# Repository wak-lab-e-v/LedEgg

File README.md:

# LedEgg

WAK-Lab project 
* Atiny 25/45/85 based
* 3 74HC595D 8-bit serial-in, serial or parallel-out shift register with output latches
* 21 LEDs

## Led chain
3 positions are not connectet to a led but take a place in the serial stream of 3 bytes

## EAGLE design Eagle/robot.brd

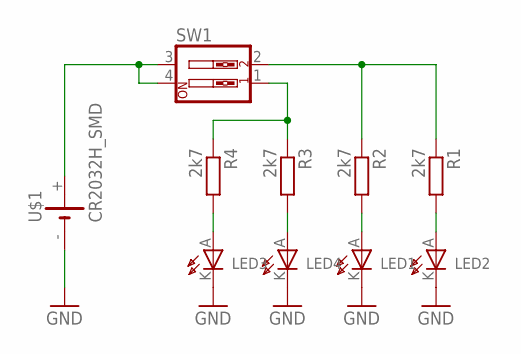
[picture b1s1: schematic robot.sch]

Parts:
LED1, LED2: LEDREAR; 3MM_REAR
LED3, LED4: LED3MMH; 3MM_H
R1, R2, R3, R4: 2k7; 0204/7
SW1: SW_DIP-2; EDG-02
U$1: CR2032H_SMD

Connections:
GND: LED1.K, LED2.K, LED3.K, LED4.K, U$1.-
unnamed: LED4.A, R3.2
unnamed: LED3.A, R4.2
unnamed: R1.1, R2.1, SW1.2
unnamed: R3.1, R4.1, SW1.1
unnamed: SW1.3, SW1.4, U$1.+
unnamed: LED1.A, R2.2
unnamed: LED2.A, R1.2

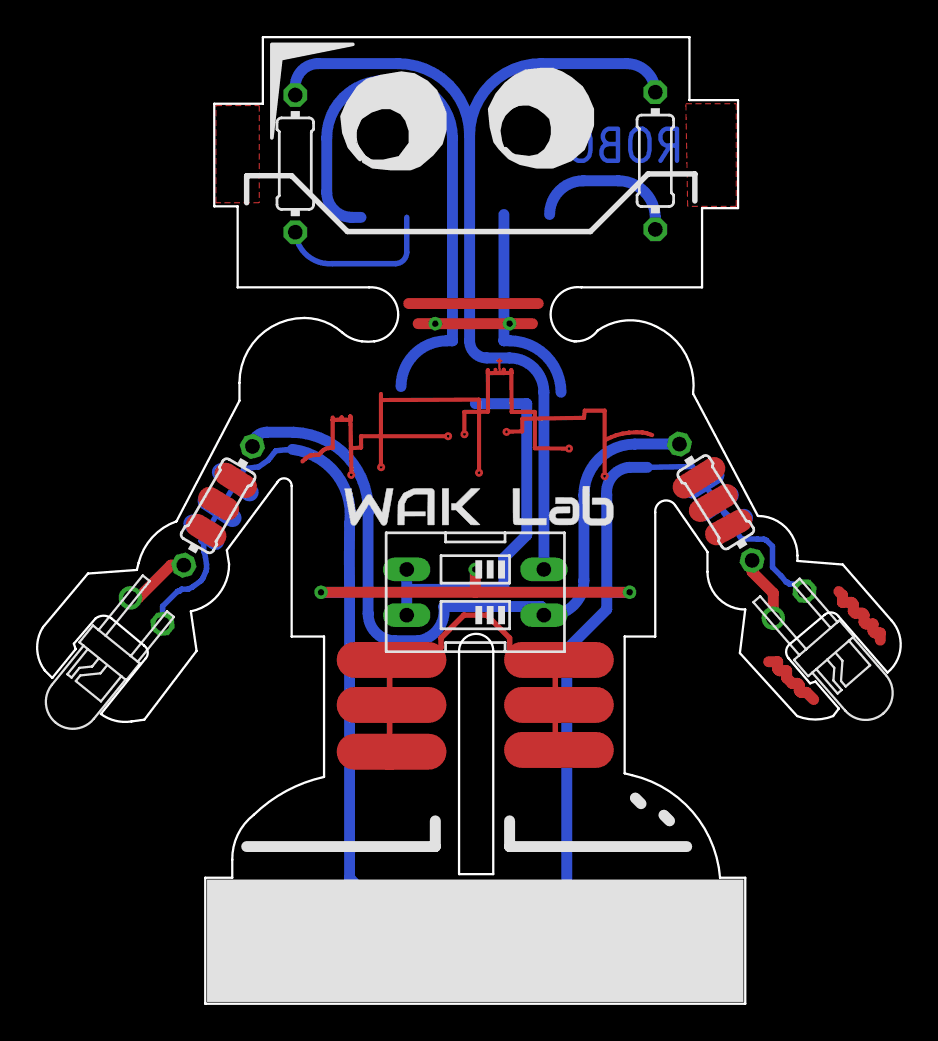
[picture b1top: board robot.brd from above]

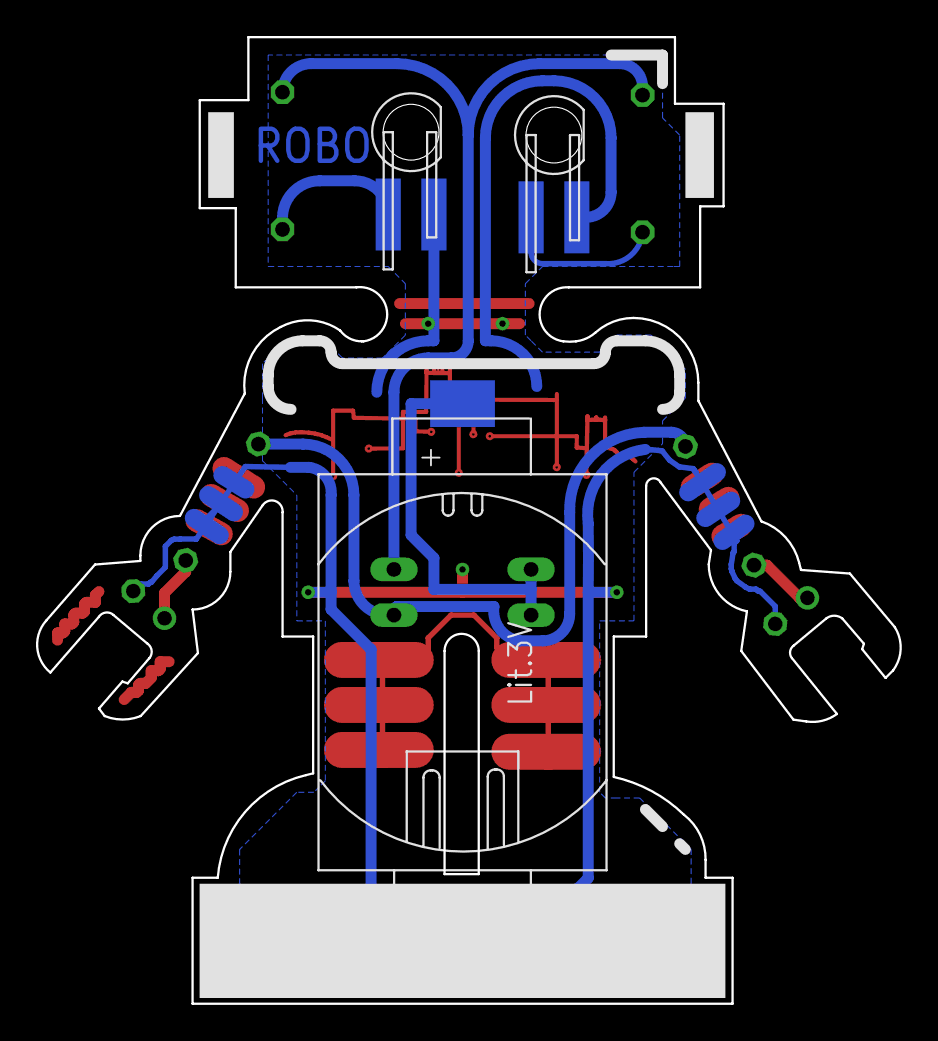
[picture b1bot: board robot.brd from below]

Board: 2 copper layers, 48.0 x 53.7 mm, 10 parts (3 on the bottom side), 8 nets.

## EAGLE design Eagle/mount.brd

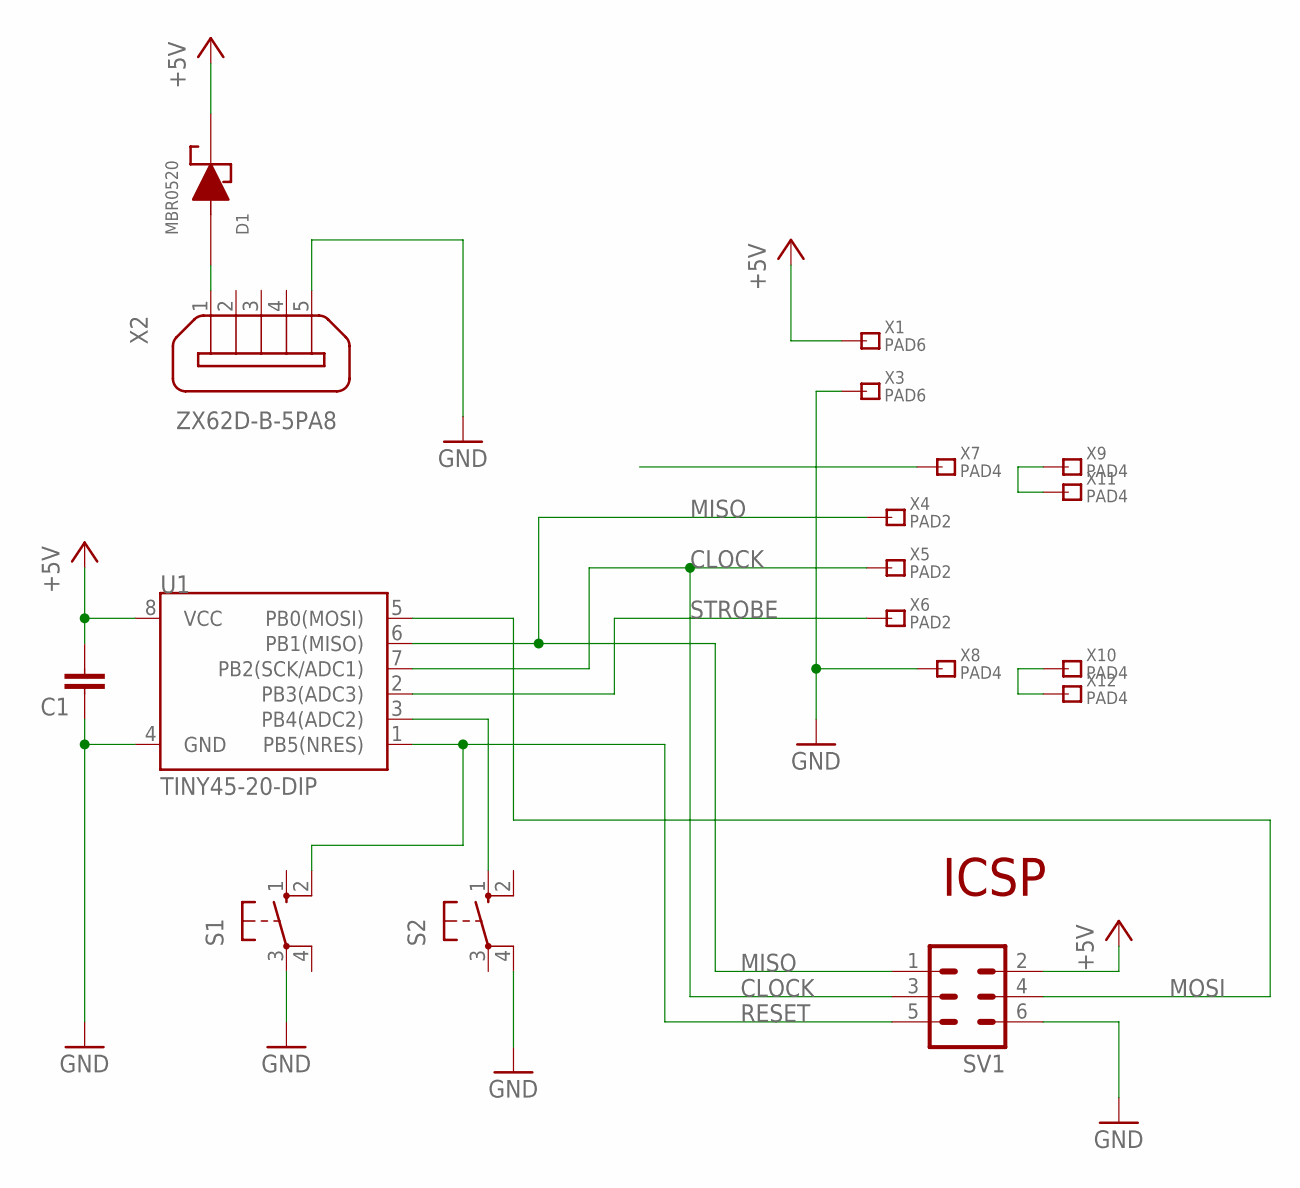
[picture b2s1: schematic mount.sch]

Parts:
C1: C-EUC0805; C0805
D1: MBR0520; SOD-123
S1, S2: 10-XX; B3F-10XX
SV1: MA03-2
U1: TINY45-20-DIP; DIP08_MCU
X1, X3: PAD6; SMDPAD
X2: ZX62D-B-5PA8
X4, X5, X6: PAD2; SMDPAD_S
X7, X8, X9, X10, X11, X12: PAD4; SMDPAD_M

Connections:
+5V: C1.2, D1.1 (CA), SV1.2, U1.8 (VCC), X1.P$1
CLOCK: SV1.3, U1.7 (PB2(SCK/ADC1)), X5.P$1
GND: C1.1, S1.3, S2.4 (P1), SV1.6, U1.4 (GND), X2.5, X3.P$1, X8.P$1
MISO: SV1.1, U1.6 (PB1(MISO)), X4.P$1
MOSI: SV1.4, U1.5 (PB0(MOSI))
unnamed: X9.P$1, X11.P$1
unnamed: X10.P$1, X12.P$1
unnamed: S2.1 (S), U1.3 (PB4(ADC2))
unnamed: D1.2 (AN), X2.1
RESET: S1.2 (S1), SV1.5, U1.1 (PB5(NRES))
STROBE: U1.2 (PB3(ADC3)), X6.P$1

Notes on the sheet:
ICSP

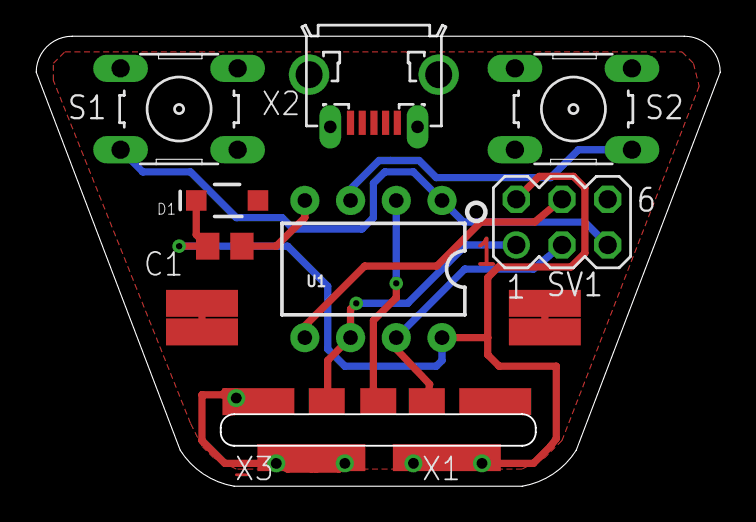
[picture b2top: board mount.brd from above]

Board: 2 copper layers, 37.9 x 24.9 mm, 18 parts (0 on the bottom side), 11 nets.

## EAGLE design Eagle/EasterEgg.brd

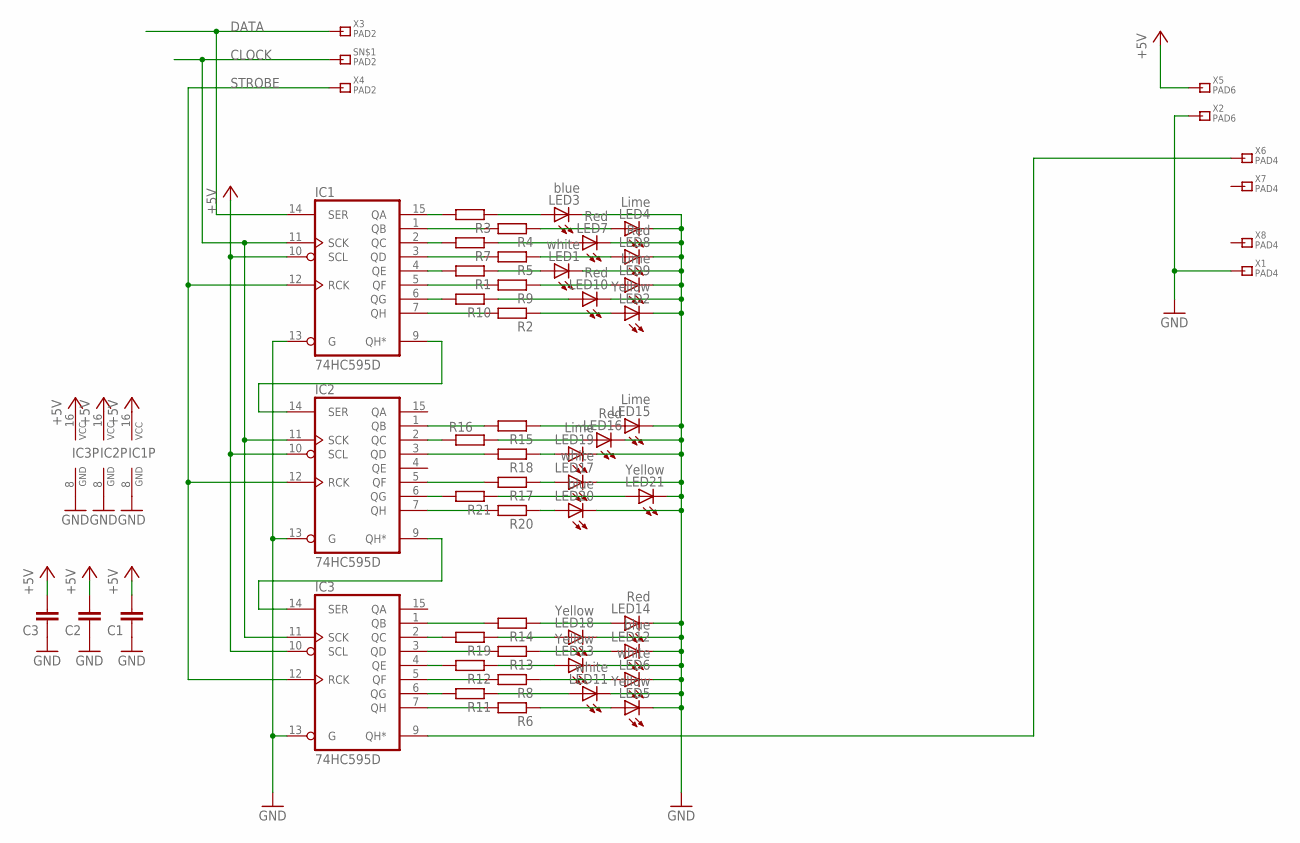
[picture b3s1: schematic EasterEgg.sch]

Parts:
C1, C2, C3: C-EUC0805; C0805
IC1, IC2, IC3: 74HC595D; SO16
LED1, LED6, LED11, LED17: white; LED3MM
LED2, LED5, LED13, LED18, LED21: Yellow; LED3MM
LED3, LED12, LED20: blue; LED3MM
LED4, LED9, LED15, LED19: Lime; LED3MM
LED7, LED8, LED10, LED14, LED16: Red; LED3MM
R1, R2, R3, R4, R5, R6, R7, R8, R9, R10, R11, R12, R13, R14, R15, R16, R17, R18, R19, R20, R21: R-EU_R1206; R1206
SN$1: PAD2; SMDPAD_S
X1, X6, X7, X8: PAD4; SMDPAD_M
X2, X5: PAD6; SMDPAD
X3, X4: PAD2; SMDPAD_S

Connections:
+5V: C1.2, C2.2, C3.2, IC1.10 (SCL), IC1.16 (VCC), IC2.10 (SCL), IC2.16 (VCC), IC3.10 (SCL), IC3.16 (VCC), X5.P$1
CLOCK: IC1.11 (SCK), IC2.11 (SCK), IC3.11 (SCK), SN$1.P$1
DATA: IC1.14 (SER), X3.P$1
GND: C1.1, C2.1, C3.1, IC1.8 (GND), IC1.13 (G), IC2.8 (GND), IC2.13 (G), IC3.8 (GND), IC3.13 (G), LED1.K (C), LED2.K (C), LED3.K (C), LED4.K (C), LED5.K (C), LED6.K (C), LED7.K (C), LED8.K (C), LED9.K (C), LED10.K (C), LED11.K (C), LED12.K (C), LED13.K (C), LED14.K (C), LED15.K (C), LED16.K (C), LED17.K (C), LED18.K (C), LED19.K (C), LED20.K (C), LED21.K (C), X1.P$1, X2.P$1
unnamed: IC1.2 (QC), R7.2
unnamed: IC1.9 (QH*), IC2.14 (SER)
unnamed: IC2.9 (QH*), IC3.14 (SER)
unnamed: LED7.A, R7.1
unnamed: IC1.1 (QB), R4.2
unnamed: LED4.A, R4.1
unnamed: IC1.15 (QA), R3.2
unnamed: LED3.A, R3.1
unnamed: IC1.7 (QH), R2.2
unnamed: LED2.A, R2.1
unnamed: IC1.3 (QD), R5.2
unnamed: IC1.4 (QE), R1.2
unnamed: IC1.5 (QF), R9.2
unnamed: IC1.6 (QG), R10.2
unnamed: IC2.1 (QB), R15.2
unnamed: IC2.2 (QC), R16.1
unnamed: IC2.3 (QD), R18.2
unnamed: IC2.7 (QH), R20.2
unnamed: IC2.5 (QF), R17.2
unnamed: IC2.6 (QG), R21.2
unnamed: IC3.2 (QC), R19.2
unnamed: IC3.1 (QB), R14.2
unnamed: IC3.5 (QF), R8.2
unnamed: IC3.4 (QE), R12.2
unnamed: IC3.3 (QD), R13.2
unnamed: IC3.6 (QG), R11.2
unnamed: IC3.7 (QH), R6.2
unnamed: LED10.A, R10.1
unnamed: LED16.A, R16.2
unnamed: LED19.A, R18.1
unnamed: LED20.A, R20.1
unnamed: LED21.A, R21.1
unnamed: LED18.A, R19.1
unnamed: LED14.A, R14.1
unnamed: LED12.A, R13.1
unnamed: LED13.A, R12.1
unnamed: LED5.A, R6.1
unnamed: LED11.A, R11.1
unnamed: LED6.A, R8.1
unnamed: LED17.A, R17.1
unnamed: LED8.A, R5.1
unnamed: LED1.A, R1.1
unnamed: LED9.A, R9.1
unnamed: LED15.A, R15.1
unnamed: IC3.9 (QH*), X6.P$1
STROBE: IC1.12 (RCK), IC2.12 (RCK), IC3.12 (RCK), X4.P$1

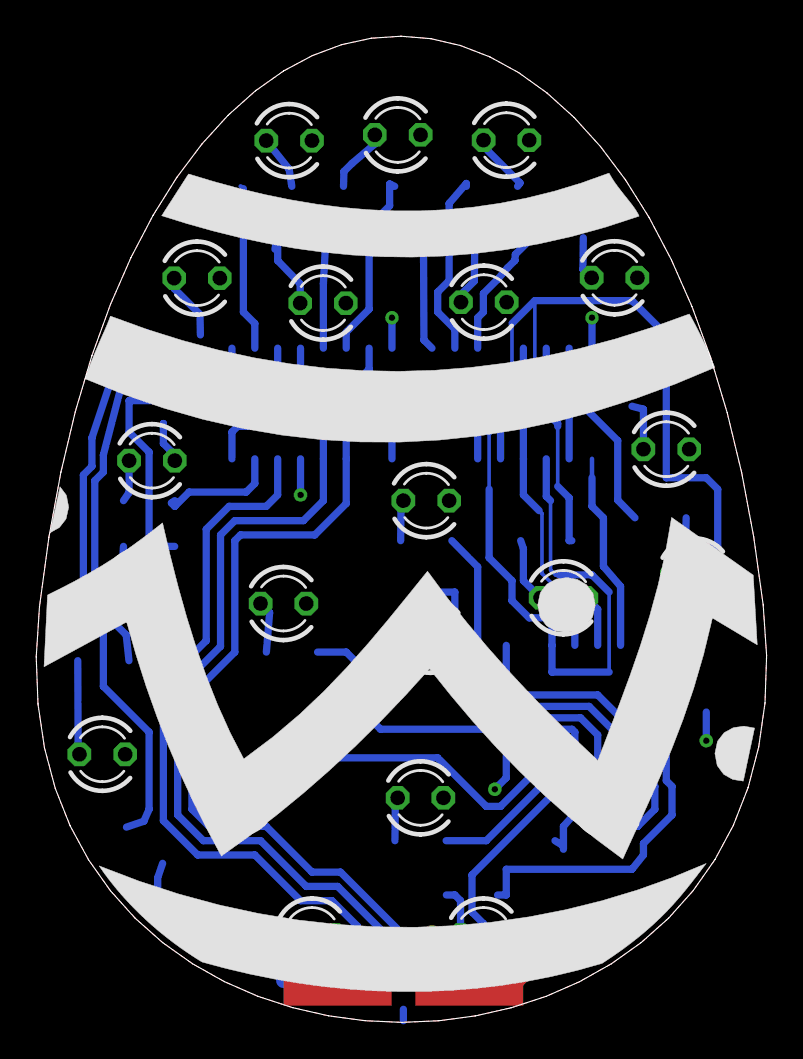
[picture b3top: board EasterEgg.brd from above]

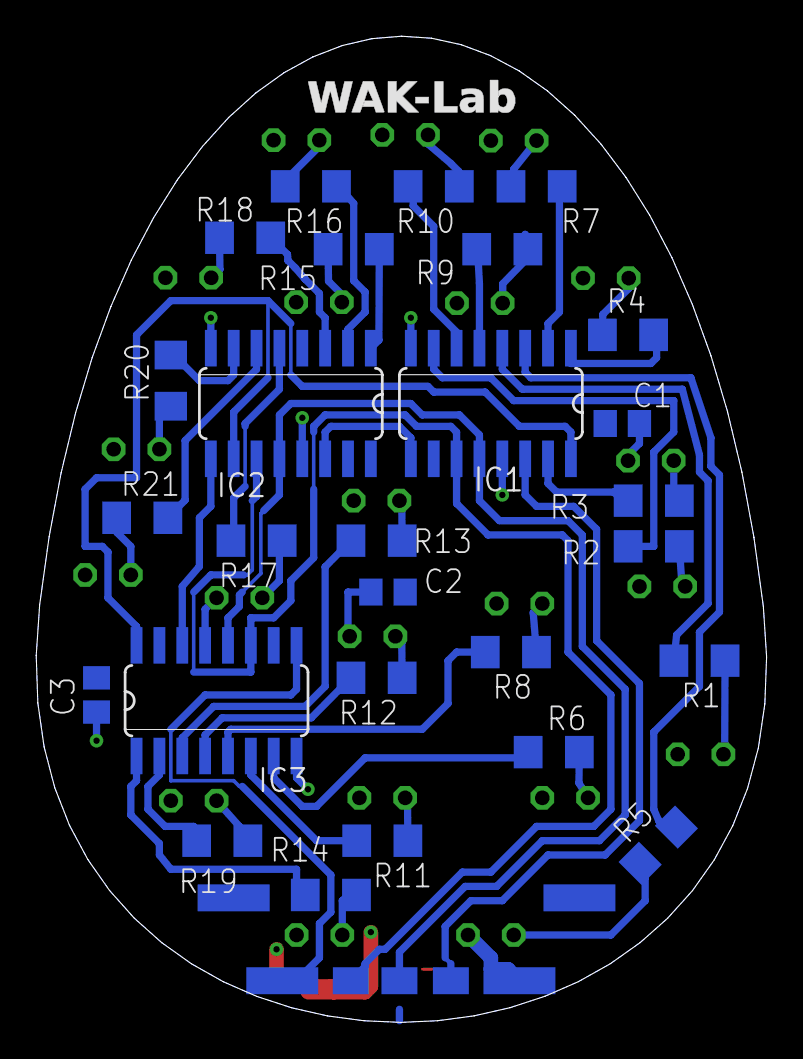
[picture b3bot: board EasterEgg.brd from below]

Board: 2 copper layers, 40.6 x 54.8 mm, 57 parts (34 on the bottom side), 50 nets.

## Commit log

2022-03-24 Hello Egg
2022-03-30 Blinken etwas langsamer
2022-04-02 Start
2022-05-10 EIn Roboter
2022-06-07 Led-Nummern hinzugefügt
2022-06-08 Handler für vordefinierte Funktionen hinzugefügt
2022-06-08 Fehler entfernt

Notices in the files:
parts and their libraries:
SparkFun-Retired: Licensing: Creative Commons ShareAlike 4.0 International - https://creativecommons.org/licenses/by-sa/4.0
